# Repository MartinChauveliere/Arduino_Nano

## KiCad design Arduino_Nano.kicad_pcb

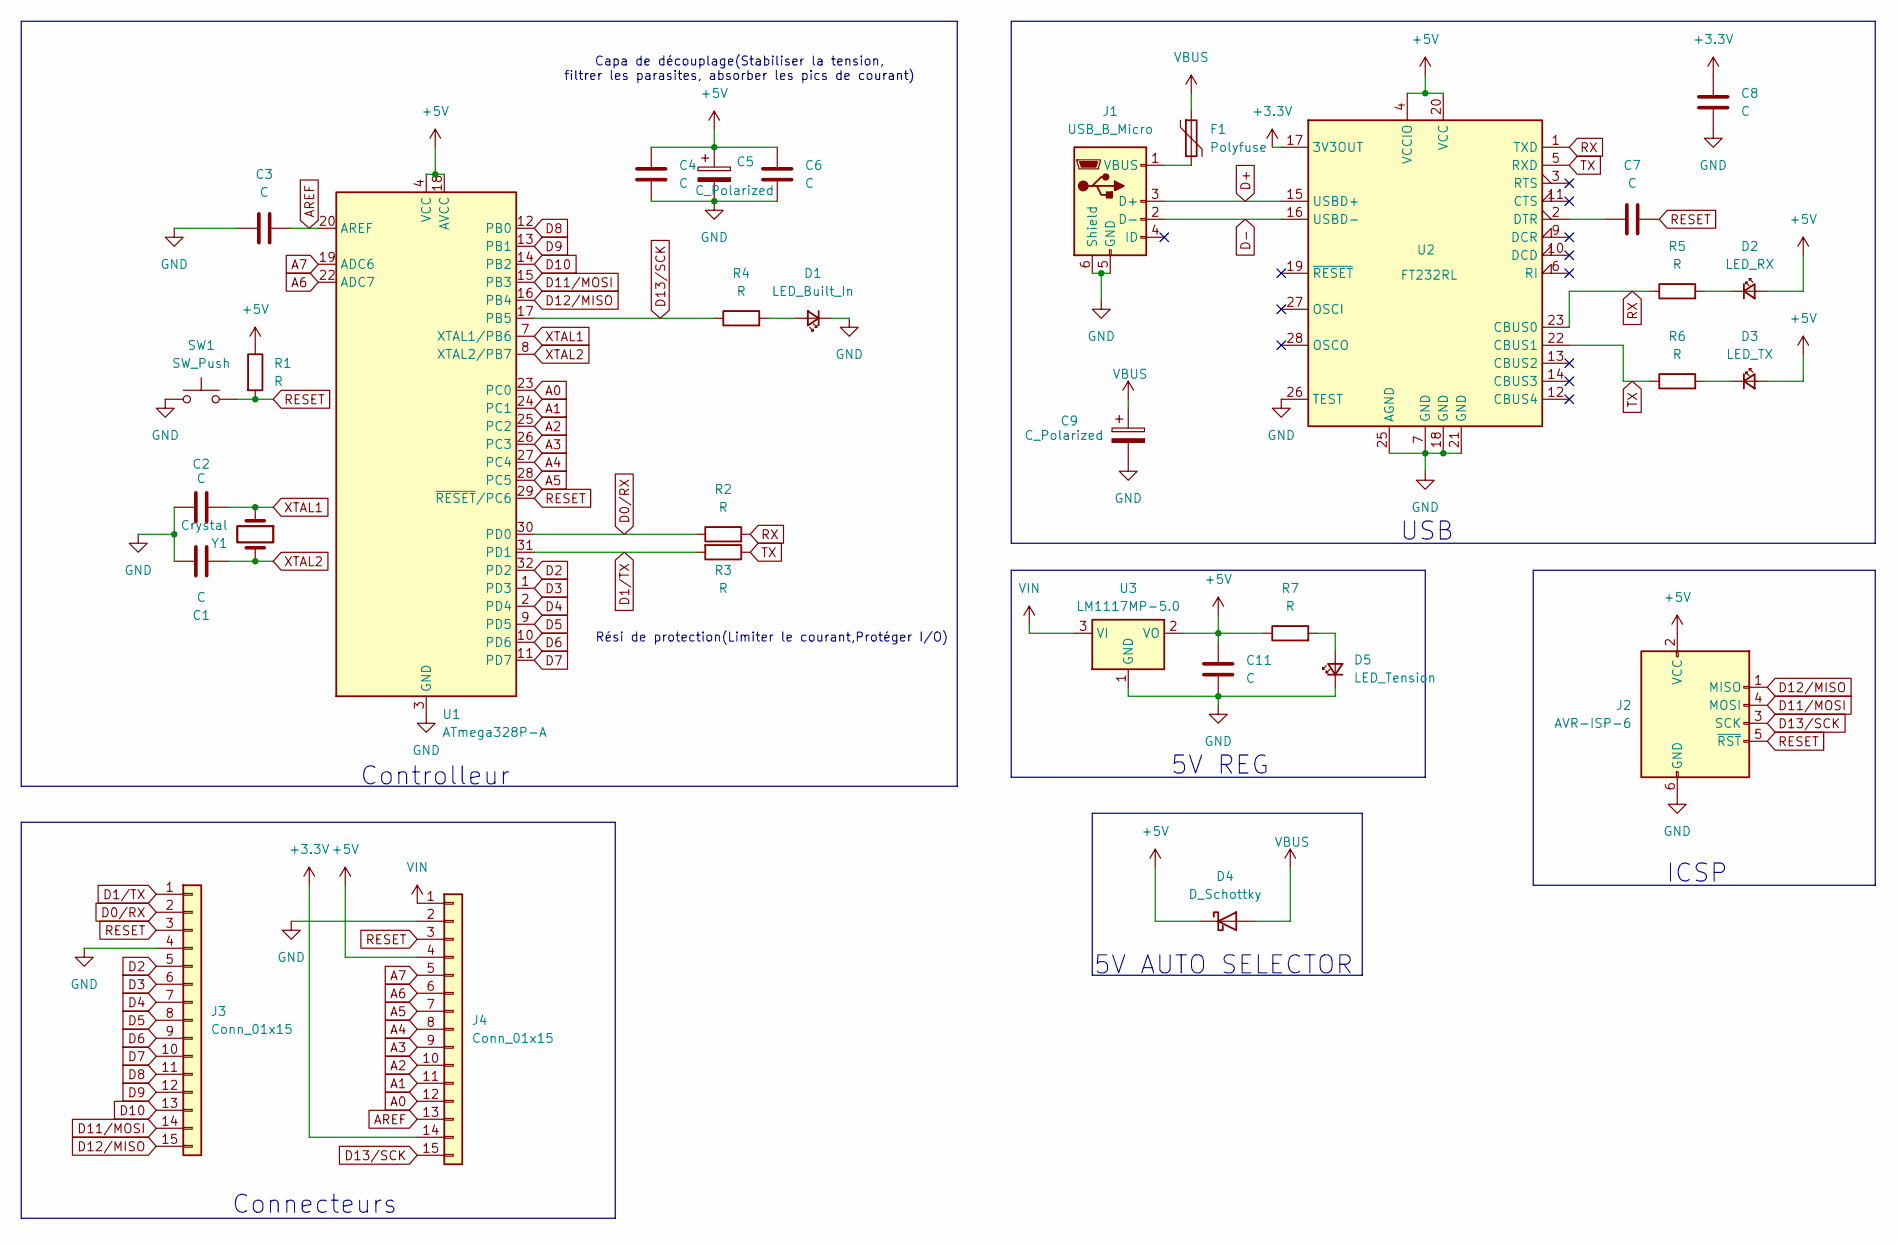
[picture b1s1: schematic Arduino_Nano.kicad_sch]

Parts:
C1, C2, C3, C4, C6, C7, C8, C11: C; C_0805_2012Metric
C5, C9: C_Polarized; C_0805_2012Metric
D1: LED_Built_In; LED_0805_2012Metric
D2: LED_RX; LED_0805_2012Metric
D3: LED_TX; LED_0805_2012Metric
D4: D_Schottky; D_SMA
D5: LED_Tension; LED_0805_2012Metric
F1: Polyfuse; Fuse_1812_4532Metric
J1: USB_B_Micro; USB_Micro-B_Molex_47346-0001
J2: AVR-ISP-6; PinHeader_2x03_P2.54mm_Vertical
J3, J4: Conn_01x15; PinHeader_1x15_P2.54mm_Vertical
R1, R2, R3, R4, R5, R6, R7: R; R_0805_2012Metric
SW1: SW_Push; SW_SPST_EVQPE1
U1: ATmega328P-A; TQFP-32_7x7mm_P0.8mm
U2: FT232RL; SSOP-28_5.3x10.2mm_P0.65mm
U3: LM1117MP-5.0; SOT-223-3_TabPin2
Y1: Crystal; Crystal_SMD_3215-2Pin_3.2x1.5mm

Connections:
+3.3V: C8.2, J4.14, U2.17 (3V3OUT)
+5V: C4.1, C5.1, C6.1, C11.2, D2.2 (A), D3.2 (A), D4.1 (K), J2.2 (VCC), J4.4, R1.1, R7.1, U1.4 (VCC), U1.6 (VCC), U1.18 (AVCC), U2.4 (VCCIO), U2.20 (VCC), U3.2 (VO)
A0: J4.12, U1.23 (PC0)
A1: J4.11, U1.24 (PC1)
A2: J4.10, U1.25 (PC2)
A3: J4.9, U1.26 (PC3)
A4: J4.8, U1.27 (PC4)
A5: J4.7, U1.28 (PC5)
A6: J4.6, U1.22 (ADC7)
A7: J4.5, U1.19 (ADC6)
AREF: C3.1, J4.13, U1.20 (AREF)
D0/RX: J3.2, R2.1, U1.30 (PD0)
D1/TX: J3.1, R3.2, U1.31 (PD1)
D2: J3.5, U1.32 (PD2)
D3: J3.6, U1.1 (PD3)
D4: J3.7, U1.2 (PD4)
D5: J3.8, U1.9 (PD5)
D6: J3.9, U1.10 (PD6)
D7: J3.10, U1.11 (PD7)
D8: J3.11, U1.12 (PB0)
D9: J3.12, U1.13 (PB1)
D10: J3.13, U1.14 (PB2)
D11/MOSI: J2.4 (MOSI), J3.14, U1.15 (PB3)
D12/MISO: J2.1 (MISO), J3.15, U1.16 (PB4)
D13/SCK: J2.3 (SCK), J4.15, R4.1, U1.17 (PB5)
D+: J1.3 (D+), U2.15 (USBD+)
D-: J1.2 (D-), U2.16 (USBD-)
GND: C1.1, C2.2, C3.2, C4.2, C5.2, C6.2, C8.1, C9.2, C11.1, D1.1 (K), D5.1 (K), J1.5 (GND), J1.6 (Shield), J2.6 (GND), J3.4, J4.2, SW1.1, U1.3 (GND), U1.5 (GND), U1.21 (GND), U2.7 (GND), U2.18 (GND), U2.21 (GND), U2.25 (AGND), U2.26 (TEST), U3.1 (GND)
unnamed: D1.2 (A), R4.2
unnamed: D2.1 (K), R5.2
unnamed: D3.1 (K), R6.2
unnamed: D5.2 (A), R7.2
unnamed: F1.2, J1.1 (VBUS)
unnamed: C7.1, U2.2 (DTR)
RESET: C7.2, J2.5 (~RST), J3.3, J4.3, R1.2, SW1.2, U1.29 (~RESET/PC6)
RX: R2.2, R5.1, U2.1 (TXD), U2.23 (CBUS0)
TX: R3.1, R6.1, U2.5 (RXD), U2.22 (CBUS1)
VBUS: C9.1, D4.2 (A), F1.1
VIN: J4.1, U3.3 (VI)
XTAL1: C2.1, U1.7 (XTAL1/PB6), Y1.1
XTAL2: C1.2, U1.8 (XTAL2/PB7), Y1.2

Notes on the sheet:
Capa de découplage(Stabiliser la tension, filtrer les parasites, absorber les pics de courant)
ICSP
5V AUTO SELECTOR
Connecteurs
Rési de protection(Limiter le courant,Protéger I/O)
5V REG
Controlleur
USB

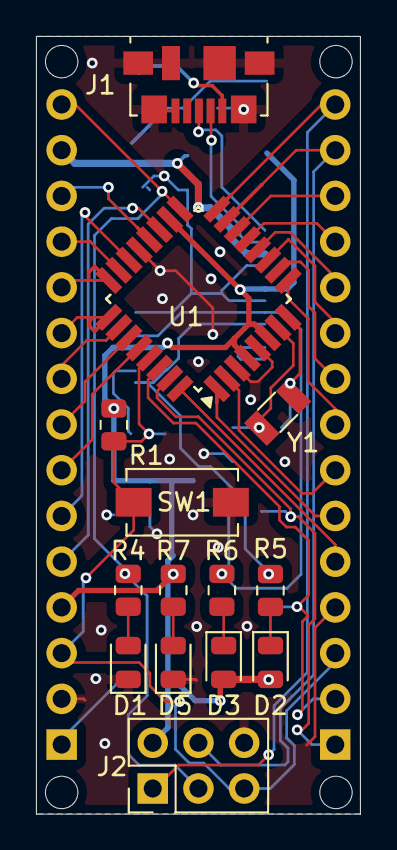
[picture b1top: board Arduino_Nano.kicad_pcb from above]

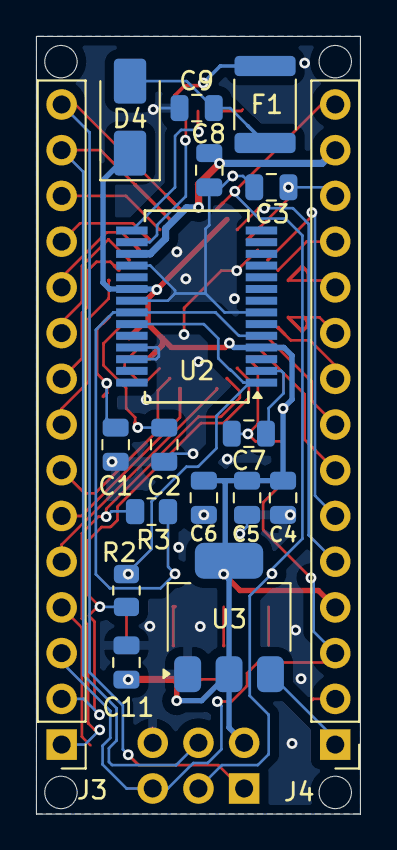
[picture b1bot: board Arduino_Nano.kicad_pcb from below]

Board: 2 copper layers, 18.0 x 43.2 mm, 32 parts (18 on the bottom side), 41 nets.

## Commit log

2025-05-09 Finished
